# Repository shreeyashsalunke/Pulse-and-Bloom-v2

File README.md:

<h5><i>Pulse and Bloom is a collaberative project done by <b>Saba Ghole, Shilo Shiv Suleman, Rohan Dixit, Heather Stewart, Luke Iseman,</b> and <b>Samuel Clay</b>. I got an opportunity to work with <b>Kavya D</b> and <b>Shilo Shiv Suleman</b> on this Art Installation<br><br>
Thanks to <b>Avijit Michael</b> and <b>Kalyani Ingole</b>.<br>
Special thanks to the amazing <b>Ankit Daftery</b> for his always supporting and helping nature.</i></h5><hr>

<br>
Pulse and Bloom is an interactive and social art installation that visualizes participants’ heartbeats and invites people to share and sync their human heartbeats in a rhythmic pattern. Pulse and Bloom is one of the largest biofeedback installations of its kind, allowing 40 people to visualize their heartbeats simultaneously.

Pulse and Bloom consists of 10 lotuses of varying heights of 10 to 14 feet with pulse sensors mounted on the base of the stem. When a participant places their hand upon the pulse sensor, the stem and the flower in the sky start to beat with their heart. Furthermore, when more than one person places their hand upon the pulse sensor, the stem starts to pulse with both participants’ heartbeats, making it possible to watch how heart rates of different people in intimate spaces start to beat in sync, much like fireflies flashing in patterns.

Arranged in a circular matrix, the 10 lotuses contain LED lights wrapped around their stems and LEDs inside the flowers at the top that are activated when individual participants physically interact with the lotus. Each lotus is equipped with two pulse sensors, each located on a Hamsa Hand, that when pressed by one or two participants translates the participants’ heartbeat into pulsing LED lights within the lotus, visually projecting their heart into the flower in the sky. As more people begin to interact with the different lotuses, visualizing their heartbeats in pulsing lights, we begin to see the effects of each person’s heartbeat on the other and the effect of meditative synchronicity unfold.

<h2>Background by Shilo Shiv Suleman</h2>
Connection is at the core of human experience. All traditional cultures have had their spaces of ‘communion’ - of coming together and sharing. These sacred spaces were intensely personal, yet became a focal point to gather and connect.

Through our art installation Pulse and Bloom, we want to use technology to make our inner invisible worlds more visible. Using visual representations of our inner state, we aim to create group experiences of magical synchronicity that make us more aware as individuals and more connected as a community.

Remembering the ancient philosophers and mystics that spoke of the human heart as the vehicle for union between individual and environment, we wish to recreate this experience through modern heart-quantifying biosensors embedded within public art. Scientific studies show that people who spend a few moments connecting with each other, in time can sync their heartbeats to one another. We’d like to see if having public art as a mirror for this can enable people to connect better and with minimal barriers.

<h2>Interactions</h2>
Each lotus flower is blue until a person or two sits down at its base and places their hand on the pulse sensor. There is a Hamsa hand at the base of the lotus and its embedded pulse sensor. When a pulse is read, the lotus flower shoots the heartbeat up the stem and into the petals, where it blooms in a brilliant display of amber. When two people's hands are being measured, both of their heartbeats are shown as two distinct colors.

<style>.embed-container { position: relative; padding-bottom: 56.25%; height: 0; overflow: hidden; max-width: 100%; } .embed-container iframe, .embed-container object, .embed-container embed { position: absolute; top: 0; left: 0; width: 100%; height: 100%; }</style><div class='embed-container'><iframe src='https://player.vimeo.com/video/208532071' frameborder='0' webkitAllowFullScreen mozallowfullscreen allowFullScreen></iframe></div>
<br>
<style>.embed-container { position: relative; padding-bottom: 56.25%; height: 0; overflow: hidden; max-width: 100%; } .embed-container iframe, .embed-container object, .embed-container embed { position: absolute; top: 0; left: 0; width: 100%; height: 100%; }</style><div class='embed-container'><iframe src='https://player.vimeo.com/video/208532049' frameborder='0' webkitAllowFullScreen mozallowfullscreen allowFullScreen></iframe></div>

<h2>Building up the Installation</h2>
The installation was divided into 3 major parts:<br>
- <a href="#electronics">The Electronics</a><br>
- <a href="#software">The Software</a><br>
- <a href="#fab">Fabrication of the Lotus Structure and the Aesthetics</a><br>
<hr>

<p></p>
<h2>The Electronics</h2>
The electronics was further divided into 4 stages:<br>
- <a href="#boards">Making the custom circuit boards</a><br>
- <a href="#pulse-sensors">Making the custom pulse sensors</a><br>
- <a href="#leds">Driving the high current LEDs</a><br>
- <a href="#power">Powering the lotuses</a><br>
- <a href="#power">Endless cycle of Testing and Debugging :P</a><br>

<p></p>
<h3>Making the custom circuit boards</h3>
The main circuit board controls 2 addressable RGB LED Neopixel Strip, 3 sets of 3 (i.e. 9) High Power RGB LEDs and takes input from 2 pulse sensors. The LED Strip and the High Power RGB LEDs runs on 12V supply, the ATMega328p microcontrollers runs on 5V and the Pulse Sensors run 3.3V.
<br><br>
To convert 12V to 5V, I used an off-the-shelf voltage regulator. This required a +/- connection for both 12V in and 5V out. To convert 5V to 3.3V I used a SMD linear voltage regulator which was soldered directly on the board. The trace to the LED strip and High Power LEDs were thickened to provide upto 3A of current rating, while they consumed only around 1A current to avoid heat dissipation. Finally, all of the terminations are made using 2.5mm and 3.5mm pitch screw terminals.
<figure><center>
<figcaption align="center"><h5>Board Schematics</h5></figcaption></center></figure>
<figure><center></center>
<figcaption align="center"><h5>Board Layout</h5></figcaption></figure>

<p></p>
<h3>Making the custom pulse sensors</h3>
The Pulse Sensor was built by the design made by <i>Samuel Clay</i>. <br>
Link to the schematics and the brd file <a href="https://github.com/samuelclay/pulse-bloom/tree/master/pulse%20eagle">here</a>.<br>
<figure><center>
<figcaption align="center"><h5>Pulse Sensor Schematics</h5></figcaption></center></figure>
<figure><center>
<figcaption align="center"><h5>Pulse Sensor Board Layout</h5></figcaption></center></figure>

<p></p>
<h3>Driving the high current LEDs</h3>
There are 9 high power LEDs per lotus, split into groups of three, each driven by a constant current driver. Normally a single LED is powered by a single constant current driver. This driver can drive up to 1A of current at 12V. Because we were only using a single channel of color (blue) in the rest state, which is where the lotus spent most of its time, we could triple the number of LEDs driven by a single constant current driver.
<br><br>
We bought these High Power LEDs from a chineese distributor over buying it from Sparkfun. This saved a lot of monet. On the contrary we bought the original picobucks from Sparkfun. We ordered 200 odd LEDs, from which 5% had issues like LED leg broken, one colour not working and so on.
<center>

</center>

<p></p>
<h3>Powering the lotuses</h3>

<h3>Endless cycle of Testing and Debugging :P</h3>

<p></p>
<h2>The Software</h2>

<p></p>
<h2>Fabrication of the Lotus Structure and the Aesthetics</h2>

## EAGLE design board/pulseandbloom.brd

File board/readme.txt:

Before printing check if the GRD plane is present. The file should like the screenshoots in the folder.

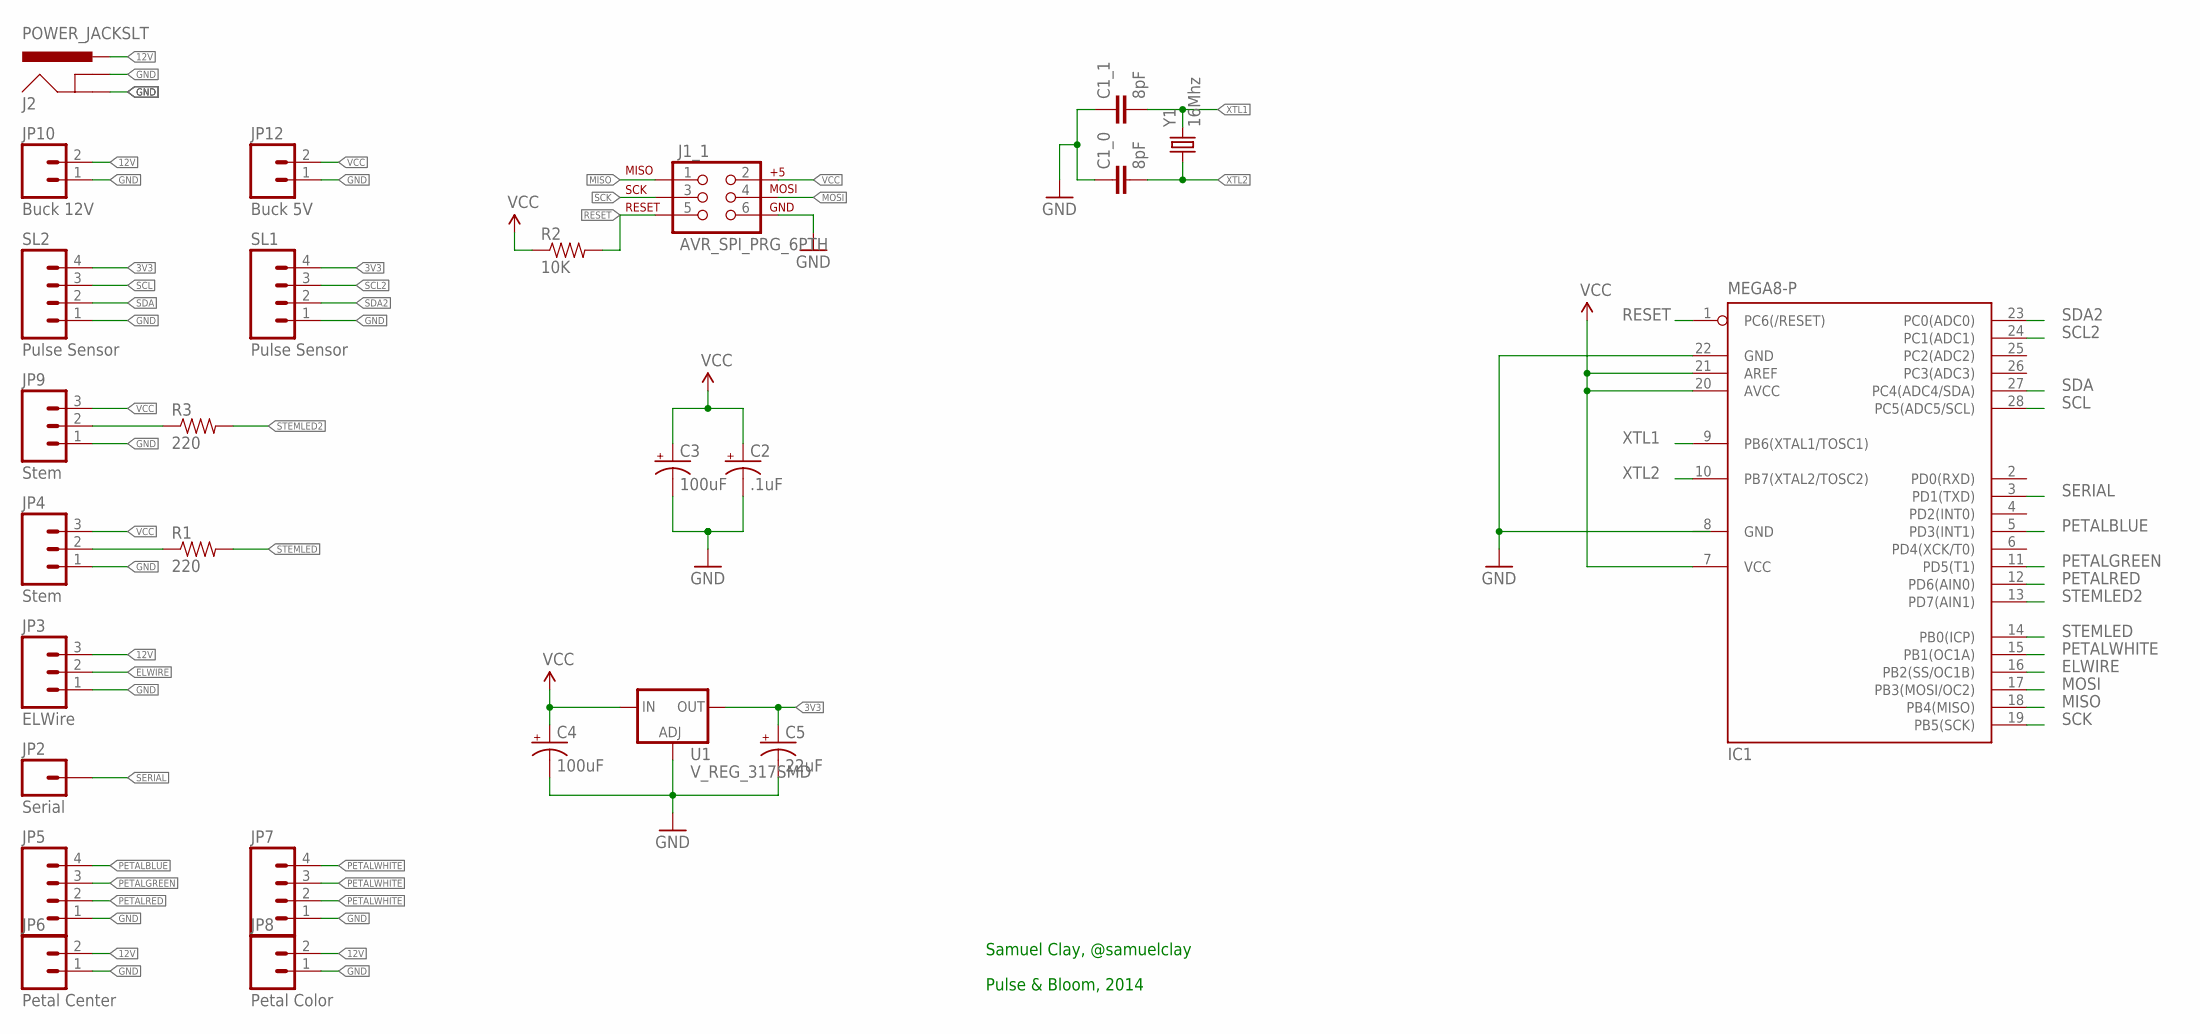
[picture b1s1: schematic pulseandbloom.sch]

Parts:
C1_0, C1_1: 8pF; CAP-PTH-5MM
C2: .1uF; CPOL-RADIAL-10UF-25V
C3, C4: 100uF; CPOL-RADIAL-100UF-25V
C5: 22uF; CPOL-RADIAL-100UF-25V
IC1: MEGA8-P; DIL28-3
J1_1: AVR_SPI_PRG_6PTH; 2X3
J2: POWER_JACKSLT; POWER_JACK_SLOT
JP2: Serial; 1X01
JP3: ELWire; MOLEX-1X3_LOCK
JP4, JP9: Stem; MOLEX-1X3_LOCK
JP5: M04POLAR_LOCK; MOLEX-1X4_LOCK
JP6: Petal Center; SCREWTERMINAL-3.5MM-2_LOCK
JP7: M04POLAR; MOLEX-1X4
JP8: Petal Color; SCREWTERMINAL-3.5MM-2_LOCK
JP10: Buck 12V; SCREWTERMINAL-3.5MM-2_LOCK
JP12: Buck 5V; SCREWTERMINAL-3.5MM-2_LOCK
R1, R3: 220; AXIAL-0.4
R2: 10K; AXIAL-0.4
SL1, SL2: Pulse Sensor; MOLEX-1X4_LOCK
U1: V_REG_317SMD; SOT223
Y1: 16Mhz; HC49US

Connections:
3V3: C5.1 (+), SL1.4, SL2.4, U1.2 (OUT)
12V: J2.PWR, JP3.3, JP6.2, JP8.2, JP10.2
ELWIRE: IC1.16 (PB2(SS/OC1B)), JP3.2
GND: C1_0.1, C1_1.1, C2.2 (-), C3.2 (-), C4.2 (-), C5.2 (-), IC1.8 (GND), IC1.22 (GND), J1_1.6, J2.GND@1 (GNDBREAK), J2.GND@2 (GND), JP3.1, JP4.1, JP5.1, JP6.1, JP7.1, JP8.1, JP9.1, JP10.1, JP12.1, SL1.1, SL2.1, U1.1 (ADJ)
MISO: IC1.18 (PB4(MISO)), J1_1.1
MOSI: IC1.17 (PB3(MOSI/OC2)), J1_1.4
unnamed: JP9.2, R3.P$1 (1)
unnamed: JP4.2, R1.P$1 (1)
PETALBLUE: IC1.5 (PD3(INT1)), JP5.4
PETALGREEN: IC1.11 (PD5(T1)), JP5.3
PETALRED: IC1.12 (PD6(AIN0)), JP5.2
PETALWHITE: IC1.15 (PB1(OC1A)), JP7.2, JP7.3, JP7.4
RESET: IC1.1 (PC6(/RESET)), J1_1.5, R2.P$2 (2)
SCK: IC1.19 (PB5(SCK)), J1_1.3
SCL: IC1.28 (PC5(ADC5/SCL)), SL2.3
SCL2: IC1.24 (PC1(ADC1)), SL1.3
SDA: IC1.27 (PC4(ADC4/SDA)), SL2.2
SDA2: IC1.23 (PC0(ADC0)), SL1.2
SERIAL: IC1.3 (PD1(TXD)), JP2.1
STEMLED: IC1.14 (PB0(ICP)), R1.P$2 (2)
STEMLED2: IC1.13 (PD7(AIN1)), R3.P$2 (2)
VCC: C2.1 (+), C3.1 (+), C4.1 (+), IC1.7 (VCC), IC1.20 (AVCC), IC1.21 (AREF), J1_1.2, JP4.3, JP9.3, JP12.2, R2.P$1 (1), U1.3 (IN)
XTL1: C1_1.2, IC1.9 (PB6(XTAL1/TOSC1)), Y1.2
XTL2: C1_0.2, IC1.10 (PB7(XTAL2/TOSC2)), Y1.1

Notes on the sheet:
Samuel Clay, @samuelclay
Pulse & Bloom, 2014

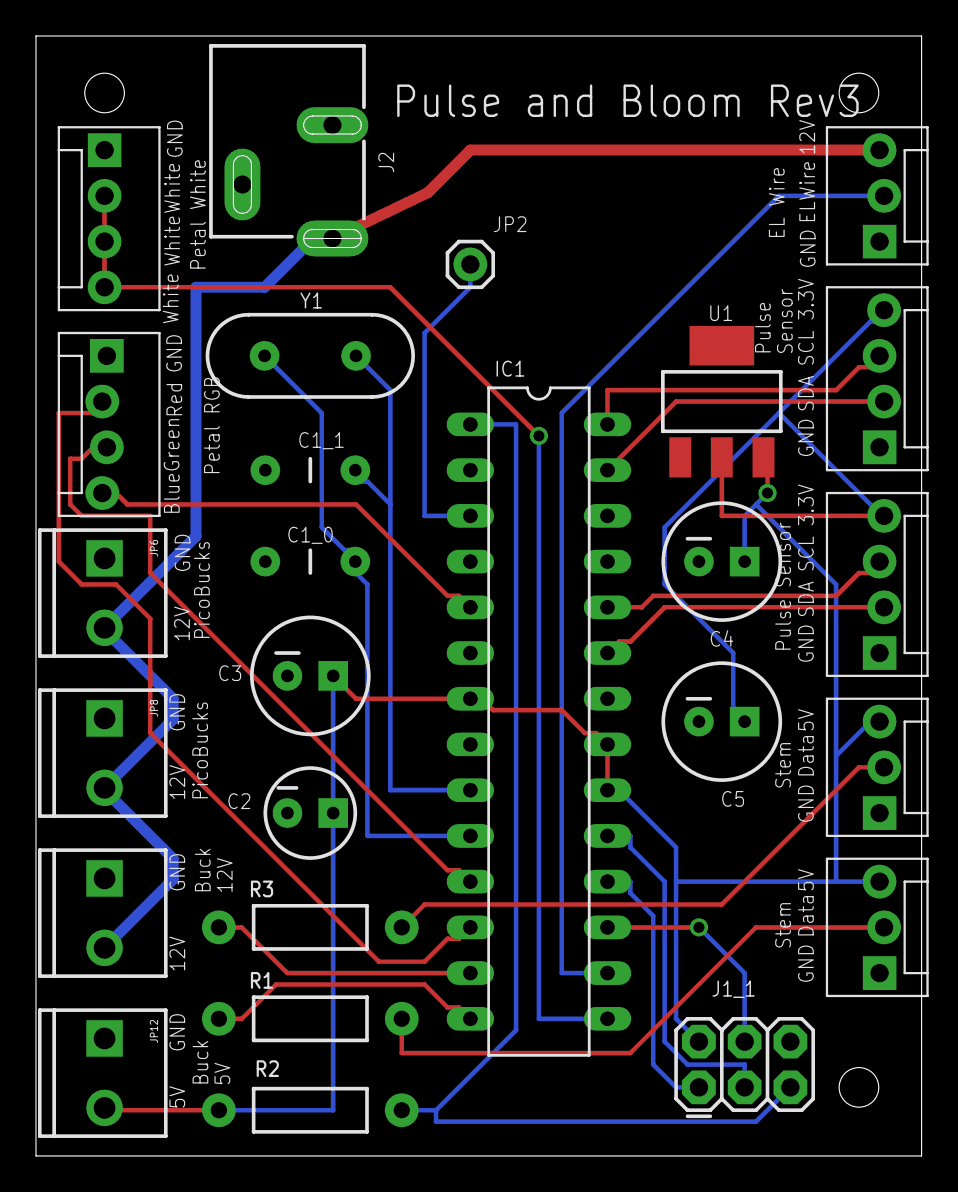
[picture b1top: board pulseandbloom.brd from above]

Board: 2 copper layers, 49.2 x 62.2 mm, 26 parts (0 on the bottom side), 24 nets.

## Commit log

2017-03-15 Set theme jekyll-theme-cayman
2017-03-15 update - concept note
2017-03-15 added images and credit
2017-03-15 added video
2017-03-15 added photos
2017-03-15 added vimeo videos
2017-03-16 added board design

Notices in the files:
parts and their libraries:
SparkFun-Capacitors: Licensing: CC v3.0 Share-Alike You are welcome to use this library for commercial purposes.
SparkFun-Passives: Licensing: Creative Commons ShareAlike 4.0 International - https://creativecommons.org/licenses/by-sa/4.0
